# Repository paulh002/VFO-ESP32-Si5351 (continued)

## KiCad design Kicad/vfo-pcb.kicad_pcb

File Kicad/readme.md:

PCB files.
Added a pi attenuation circuit in the emmitor circuit of the driver transistors. The output level was sometimes to high creating spurs and AVC to react. Now it is possible to lower the output level by add in 6db attenuation. (This is optional if resistors are ommited you have full drive level).
To use this version with Wifi add a 4700 uf capacitor to the 5v line

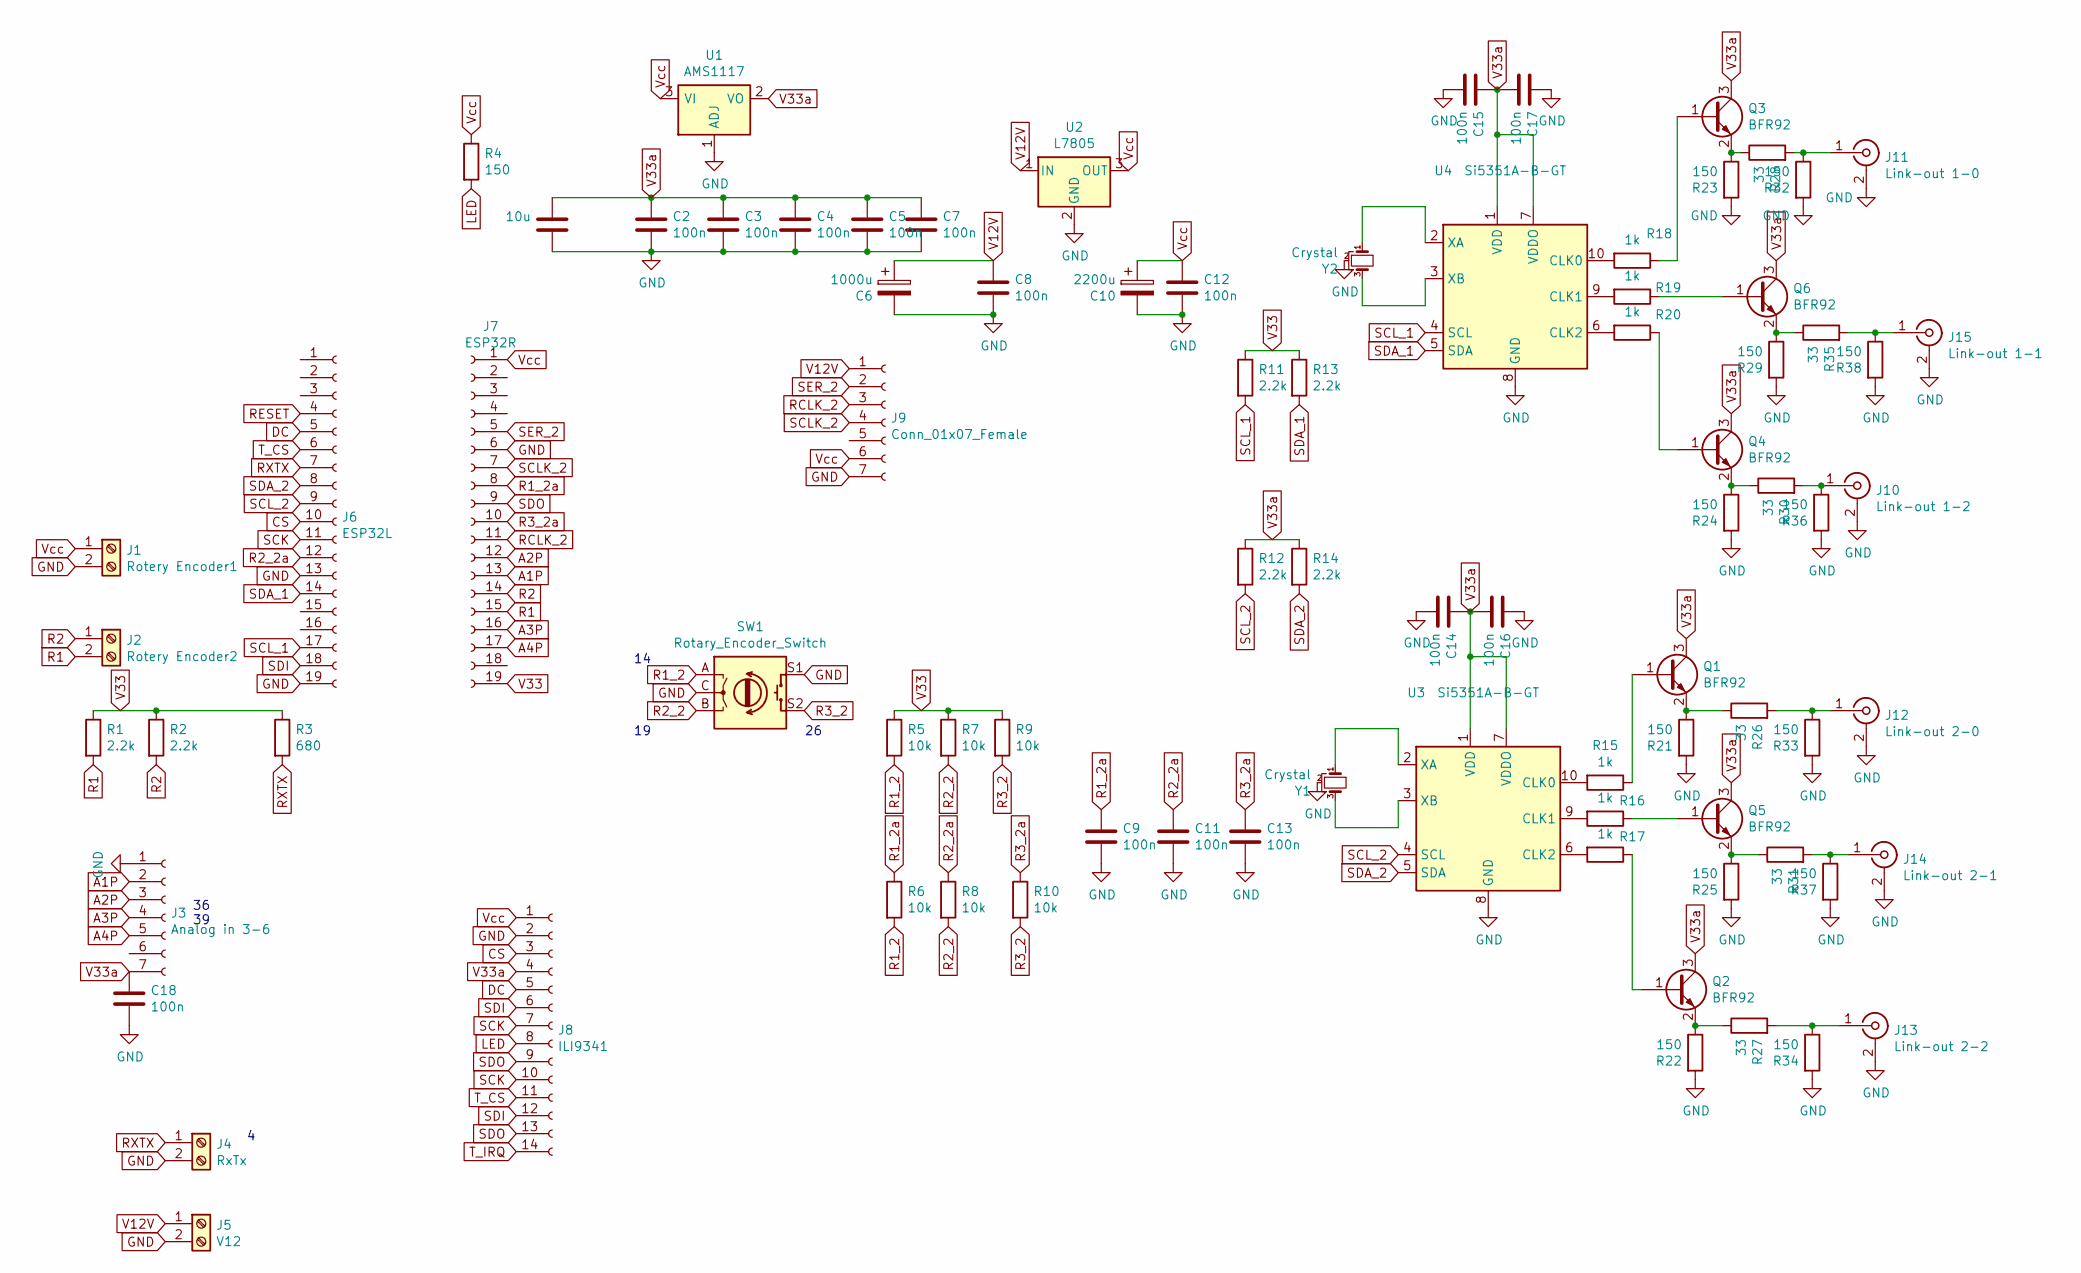
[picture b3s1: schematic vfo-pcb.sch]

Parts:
C1: 10u; C_1206_3216Metric_Pad1.42x1.75mm_HandSolder
C2, C3, C4, C5, C7, C8, C9, C11, C12, C13, C14, C15, C16, C17, C18: 100n; C_1206_3216Metric_Pad1.42x1.75mm_HandSolder
C6: 1000u; CP_Radial_D10.0mm_P5.00mm
C10: 2200u; CP_Radial_D10.0mm_P5.00mm
J1: Rotery Encoder1; TerminalBlock_MetzConnect_Type011_RT05502HBWC_1x02_P5.00mm_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
J2: Rotery Encoder2; TerminalBlock_MetzConnect_Type011_RT05502HBWC_1x02_P5.00mm_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
J3: Analog in 3-6; PinSocket_1x07_P2.54mm_Vertical
J4: RxTx; TerminalBlock_MetzConnect_Type011_RT05502HBWC_1x02_P5.00mm_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
J5: V12; TerminalBlock_MetzConnect_Type011_RT05502HBWC_1x02_P5.00mm_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
J6: ESP32L; PinSocket_1x19_P2.54mm_Vertical
J7: ESP32R; PinSocket_1x19_P2.54mm_Vertical
J8: ILI9341; PinSocket_1x14_P2.54mm_Vertical
J9: Conn_01x07_Female; PinSocket_1x07_P2.54mm_Vertical
J10: Link-out 1-2; SMA_Amphenol_132134_Vertical
J11: Link-out 1-0; SMA_Amphenol_132134_Vertical
J12: Link-out 2-0; SMA_Amphenol_132134_Vertical
J13: Link-out 2-2; SMA_Amphenol_132134_Vertical
J14: Link-out 2-1; SMA_Amphenol_132134_Vertical
J15: Link-out 1-1; SMA_Amphenol_132134_Vertical
Q1, Q2, Q3, Q4, Q5, Q6: BFR92; SOT-23
R1, R2, R11, R12, R13, R14: 2.2k; R_1206_3216Metric_Pad1.42x1.75mm_HandSolder
R3: 680; R_1206_3216Metric_Pad1.42x1.75mm_HandSolder
R4, R21, R22, R23, R24, R25, R29, R32, R33, R34, R36, R37, R38: 150; R_1206_3216Metric_Pad1.42x1.75mm_HandSolder
R5, R6, R7, R8, R9, R10: 10k; R_1206_3216Metric_Pad1.42x1.75mm_HandSolder
R15, R16, R17, R18, R19, R20: 1k; R_1206_3216Metric_Pad1.42x1.75mm_HandSolder
R26, R27, R28, R30, R31, R35: 33; R_1206_3216Metric_Pad1.42x1.75mm_HandSolder
SW1: Rotary_Encoder_Switch; RotaryEncoder_Alps_EC11E-Switch_Vertical_H20mm
U1: AMS1117; SOT-223-3_TabPin2
U2: L7805; TO-220-3_Vertical
U3, U4: Si5351A-B-GT; MSOP-10_3x3mm_P0.5mm
Y1, Y2: Crystal; Crystal_SMD_TXC_7M-4Pin_3.2x2.5mm_HandSoldering

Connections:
A1P: J3.2, J7.13
A2P: J3.3, J7.12
A3P: J3.4, J7.16
A4P: J3.5, J7.17
CS: J6.10, J8.3
DC: J6.5, J8.5
GND: C1.2, C2.1, C3.1, C4.1, C5.1, C6.2, C7.1, C8.1, C9.1, C10.2, C11.1, C12.1, C13.1, C14.1, C15.1, C16.2, C17.2, C18.1, J1.2, J3.1, J4.2, J5.2, J6.13, J6.19, J7.6, J8.2, J9.7, J10.2 (Ext), J11.2 (Ext), J12.2 (Ext), J13.2 (Ext), J14.2 (Ext), J15.2 (Ext), R21.2, R22.2, R23.2, R24.2, R25.2, R29.2, R32.2, R33.2, R34.2, R36.2, R37.2, R38.2, SW1.C, SW1.S1, U1.1 (ADJ), U2.2 (GND), U3.8 (GND), U4.8 (GND), Y1.2, Y2.2
LED: J8.8, R4.2
unnamed: J10.1 (In), R30.2, R36.1
unnamed: J11.1 (In), R28.2, R32.1
unnamed: J12.1 (In), R26.2, R33.1
unnamed: J13.1 (In), R27.2, R34.1
unnamed: J14.1 (In), R31.2, R37.1
unnamed: J15.1 (In), R35.2, R38.1
unnamed: Q1.1 (B), R15.1
unnamed: Q1.2 (E), R21.1, R26.1
unnamed: Q2.1 (B), R17.1
unnamed: Q2.2 (E), R22.1, R27.1
unnamed: Q3.1 (B), R18.1
unnamed: Q3.2 (E), R23.1, R28.1
unnamed: Q4.1 (B), R20.1
unnamed: Q4.2 (E), R24.1, R30.1
unnamed: Q5.1 (B), R16.1
unnamed: Q5.2 (E), R25.1, R31.1
unnamed: Q6.1 (B), R19.1
unnamed: Q6.2 (E), R29.1, R35.1
unnamed: R15.2, U3.10 (CLK0)
unnamed: R16.2, U3.9 (CLK1)
unnamed: R17.2, U3.6 (CLK2)
unnamed: R18.2, U4.10 (CLK0)
unnamed: R19.2, U4.9 (CLK1)
unnamed: R20.2, U4.6 (CLK2)
unnamed: U3.2 (XA), Y1.1
unnamed: U3.3 (XB), Y1.3
unnamed: U4.2 (XA), Y2.1
unnamed: U4.3 (XB), Y2.3
R1: J2.2, J7.15, R1.2
R1_2: R5.2, R6.2, SW1.A
R1_2a: C9.2, J7.8, R6.1
R2: J2.1, J7.14, R2.2
R2_2: R7.2, R8.2, SW1.B
R2_2a: C11.2, J6.12, R8.1
R3_2: R9.2, R10.2, SW1.S2
R3_2a: C13.2, J7.10, R10.1
RCLK_2: J7.11, J9.3
RESET: J6.4
RXTX: J4.1, J6.7, R3.2
SCK: J6.11, J8.7, J8.10
SCLK_2: J7.7, J9.4
SCL_1: J6.17, R11.2, U4.4 (SCL)
SCL_2: J6.9, R12.2, U3.4 (SCL)
SDA_1: J6.14, R13.2, U4.5 (SDA)
SDA_2: J6.8, R14.2, U3.5 (SDA)
SDI: J6.18, J8.6, J8.12
SDO: J7.9, J8.9, J8.13
SER_2: J7.5, J9.2
T_CS: J6.6, J8.11
T_IRQ: J8.14
V12V: C6.1, C8.2, J5.1, J9.1, U2.1 (IN)
V33: J7.19, R1.1, R2.1, R3.1, R5.1, R7.1, R9.1, R11.1, R13.1
V33a: C1.1, C2.2, C3.2, C4.2, C5.2, C7.2, C14.2, C15.2, C16.1, C17.1, C18.2, J3.7, J8.4, Q1.3 (C), Q2.3 (C), Q3.3 (C), Q4.3 (C), Q5.3 (C), Q6.3 (C), R12.1, R14.1, U1.2 (VO), U3.1 (VDD), U3.7 (VDDO), U4.1 (VDD), U4.7 (VDDO)
Vcc: C10.1, C12.2, J1.1, J7.1, J8.1, J9.6, R4.1, U1.3 (VI), U2.3 (OUT)

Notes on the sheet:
36 39

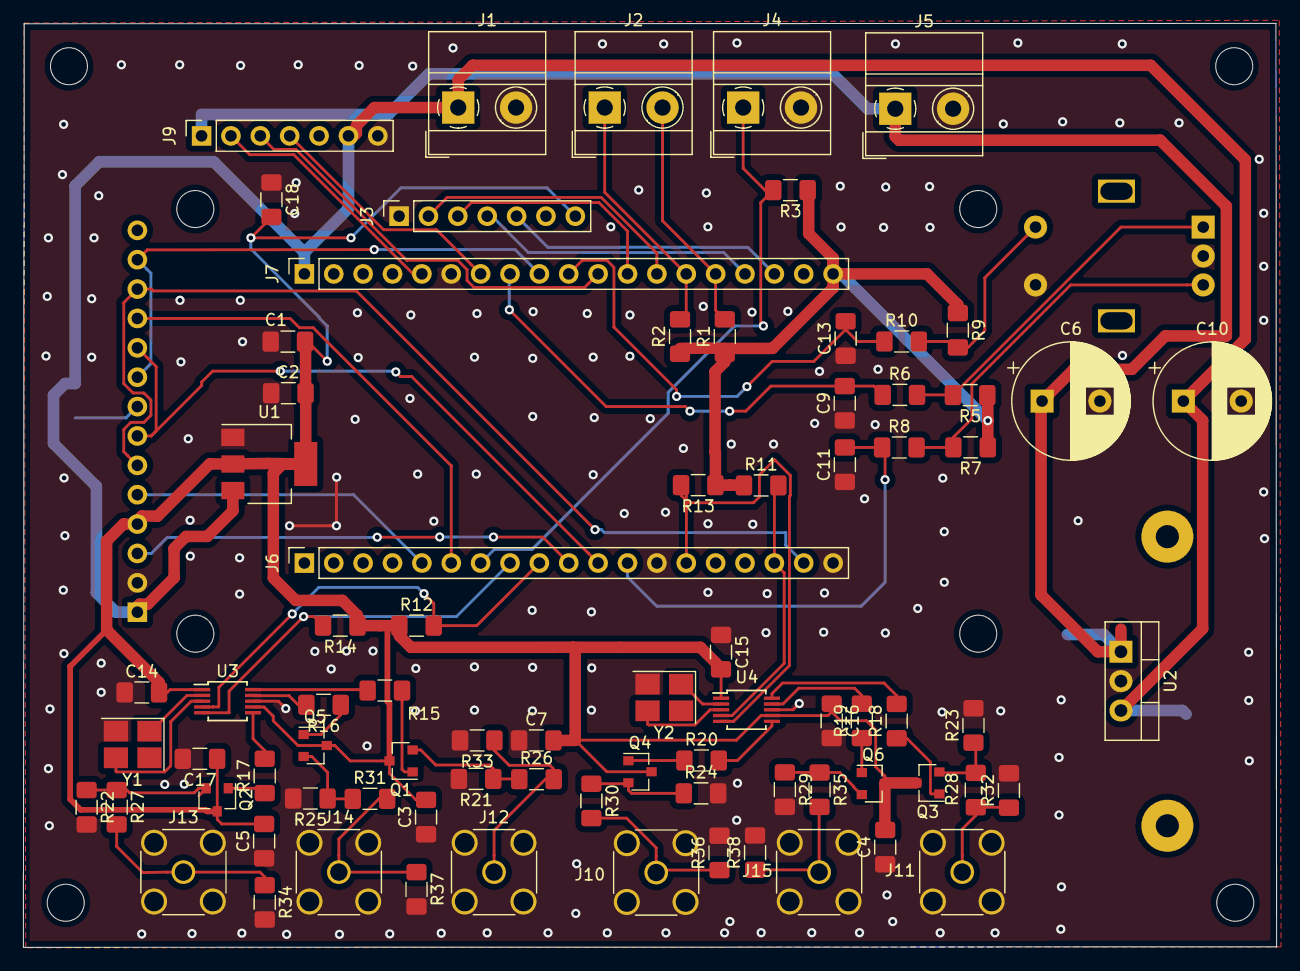
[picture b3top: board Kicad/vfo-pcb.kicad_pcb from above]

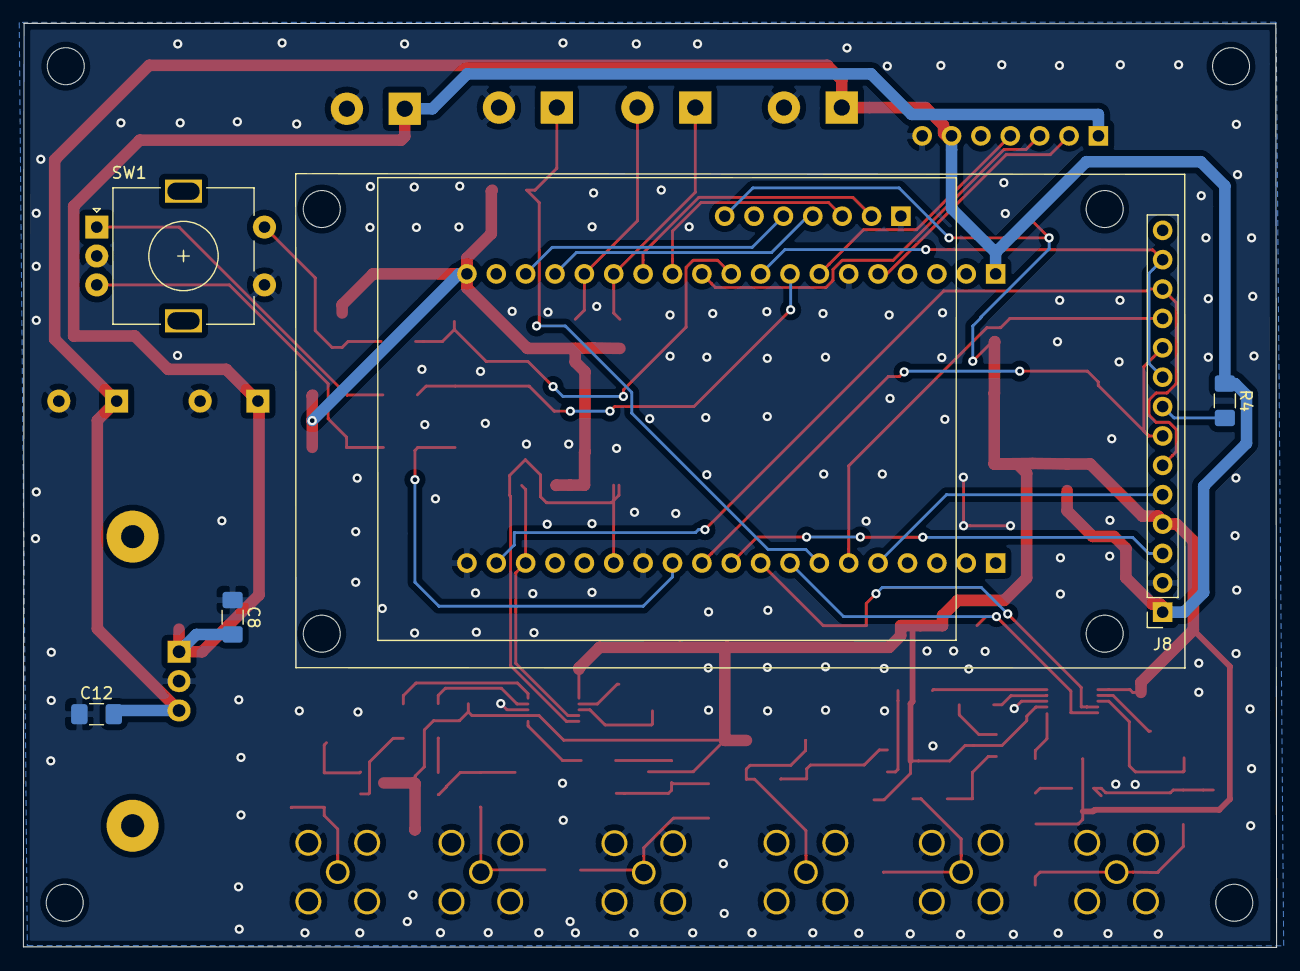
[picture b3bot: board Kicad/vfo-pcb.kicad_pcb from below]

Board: 2 copper layers, 108.4 x 79.9 mm, 94 parts (5 on the bottom side), 60 nets.

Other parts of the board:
 : MountingHole_3.2mm_M3
 #2,  #3: SolderWirePad_1x01_Drill2mm
 #4,  #5,  #6,  #7,  #8,  #9,  #10: MountingHole_3.2mm_M3

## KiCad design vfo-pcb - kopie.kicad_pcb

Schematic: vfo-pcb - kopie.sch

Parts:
C1, C3: 100u; CP_Radial_D8.0mm_P3.50mm
C2, C4, C8, C9, C10, C11, C12, C13: 100n; C_0805_2012Metric_Pad1.15x1.40mm_HandSolder
C5, C6, C7: 10n; C_0805_2012Metric_Pad1.15x1.40mm_HandSolder
J2: Conn_01x07_Female; PinSocket_1x07_P2.54mm_Vertical
J3: Si5351; PinSocket_1x07_P2.54mm_Vertical
J4: ESP32L; PinSocket_1x19_P2.54mm_Vertical
J5: ESP32R; PinSocket_1x19_P2.54mm_Vertical
J6: Rotery Encoder1; TerminalBlock_MetzConnect_Type011_RT05502HBWC_1x02_P5.00mm_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
J7: ILI9341; PinSocket_1x14_P2.54mm_Vertical
J8: Rotery Encoder2; TerminalBlock_MetzConnect_Type011_RT05502HBWC_1x02_P5.00mm_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
J9: Analog in 3-6; PinSocket_1x07_P2.54mm_Vertical
J10: Link-out 1a; SMA_Amphenol_132134_Vertical
J11: RxTx; TerminalBlock_MetzConnect_Type011_RT05502HBWC_1x02_P5.00mm_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
J13: Link-out 1b; SMA_Amphenol_132134_Vertical
J14: V12; TerminalBlock_MetzConnect_Type011_RT05502HBWC_1x02_P5.00mm_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
J17: Link-out 2a; SMA_Amphenol_132134_Vertical
J18: Link-out 3; SMA_Amphenol_132134_Vertical
J19: Link-out 2b; SMA_Amphenol_132134_Vertical
R1, R2, R7, R8, R9, R10: 2.2k; R_0805_2012Metric_Pad1.15x1.40mm_HandSolder
R3: 150; R_0805_2012Metric_Pad1.15x1.40mm_HandSolder
R4, R5, R6, R11, R12, R13: 10k; R_0805_2012Metric_Pad1.15x1.40mm_HandSolder
R14, R17, R20: 71; R_0805_2012Metric_Pad1.15x1.40mm_HandSolder
R15, R16, R18, R19, R21, R22: 100; R_0805_2012Metric_Pad1.15x1.40mm_HandSolder
SW1: Rotary_Encoder_Switch; RotaryEncoder_Alps_EC11E-Switch_Vertical_H20mm
U1, U4: AS179-92LF; SOT-363_SC-70-6
U2: 74HC595; DIP-16_W7.62mm_LongPads
U3: L7805; TO-220-3_Vertical

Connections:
A1P: J5.13, J9.2
A2P: J5.12, J9.3
A3P: J4.7, J9.4
A4P: J5.8, J9.5
A5P: J5.10, J9.6
A6P: J5.9, J9.7
CS: J4.10, J7.3
DC: J4.5, J7.5
Dout: J2.2, U2.9
GND: C1.2, C2.1, C3.2, C4.1, C5.1, C6.1, C7.1, J2.7, J3.2, J4.13, J4.19, J5.6, J6.2, J7.2, J9.1, J10.2 (Ext), J13.2 (Ext), J14.2, J17.2 (Ext), J18.2 (Ext), J19.2 (Ext), R15.2, R16.2, R18.2, R19.2, R21.2, R22.2, SW1.C, SW1.S1, U1.2, U2.8, U2.13, U3.2 (GND), U4.2
I1_1: J3.5, R20.2, R21.1
I2_1: J3.6, R17.2, R18.1
I3_1: J3.7, R14.2, R15.1
LED: J7.8, R3.2
unnamed: C8.1, R14.1, R16.1
unnamed: C8.2, U4.5
unnamed: C9.1, R17.1, R19.1
unnamed: C9.2, U1.5
unnamed: C10.1, U4.1
unnamed: C10.2, J13.1 (In)
unnamed: C11.1, U4.3
unnamed: C11.2, J10.1 (In)
unnamed: C12.1, U1.1
unnamed: C12.2, J19.1 (In)
unnamed: C13.1, U1.3
unnamed: C13.2, J17.1 (In)
unnamed: J18.1 (In), R20.1, R22.1
Qa: U1.4, U2.15, U4.4
Qb: U1.6, U2.1, U4.6
R1: J5.15, J8.2, R7.2
R1_2: R4.2, R11.2, SW1.A
R1_2a: C5.2, J4.9, R11.1
R2: J5.14, J8.1, R8.2
R2_2: R5.2, R12.2, SW1.B
R2_2a: C6.2, J4.12, R12.1
R3_2: R6.2, R13.2, SW1.S2
R3_2a: C7.2, J4.8, R13.1
RCLK_2: J2.3, J5.11, U2.12
RESET: J4.4, J7.4
RIT: J5.17, J11.2, R9.2
RXTX: J5.16, J11.1, R10.2
SCK: J4.11, J7.7
SCLK_2: J2.4, J5.7, U2.11
SCL_1: J3.4, J4.17, R1.2
SDA_1: J3.3, J4.14, R2.2
SDI: J4.18, J7.6
SDO: J7.9
SER_2: J5.5, U2.14
T_CLK: J7.10
T_CS: J7.11
T_D0: J7.13
T_DIN: J7.12
T_IRQ: J7.14
V12V: C1.1, C2.2, J2.1, J14.1, U3.1 (IN)
V33: J3.1, J5.19, R1.1, R2.1, R4.1, R5.1, R6.1, R7.1, R8.1, R9.1, R10.1
Vcc: C3.1, C4.2, J2.6, J5.1, J6.1, J7.1, R3.1, U2.10, U2.16, U3.3 (OUT)

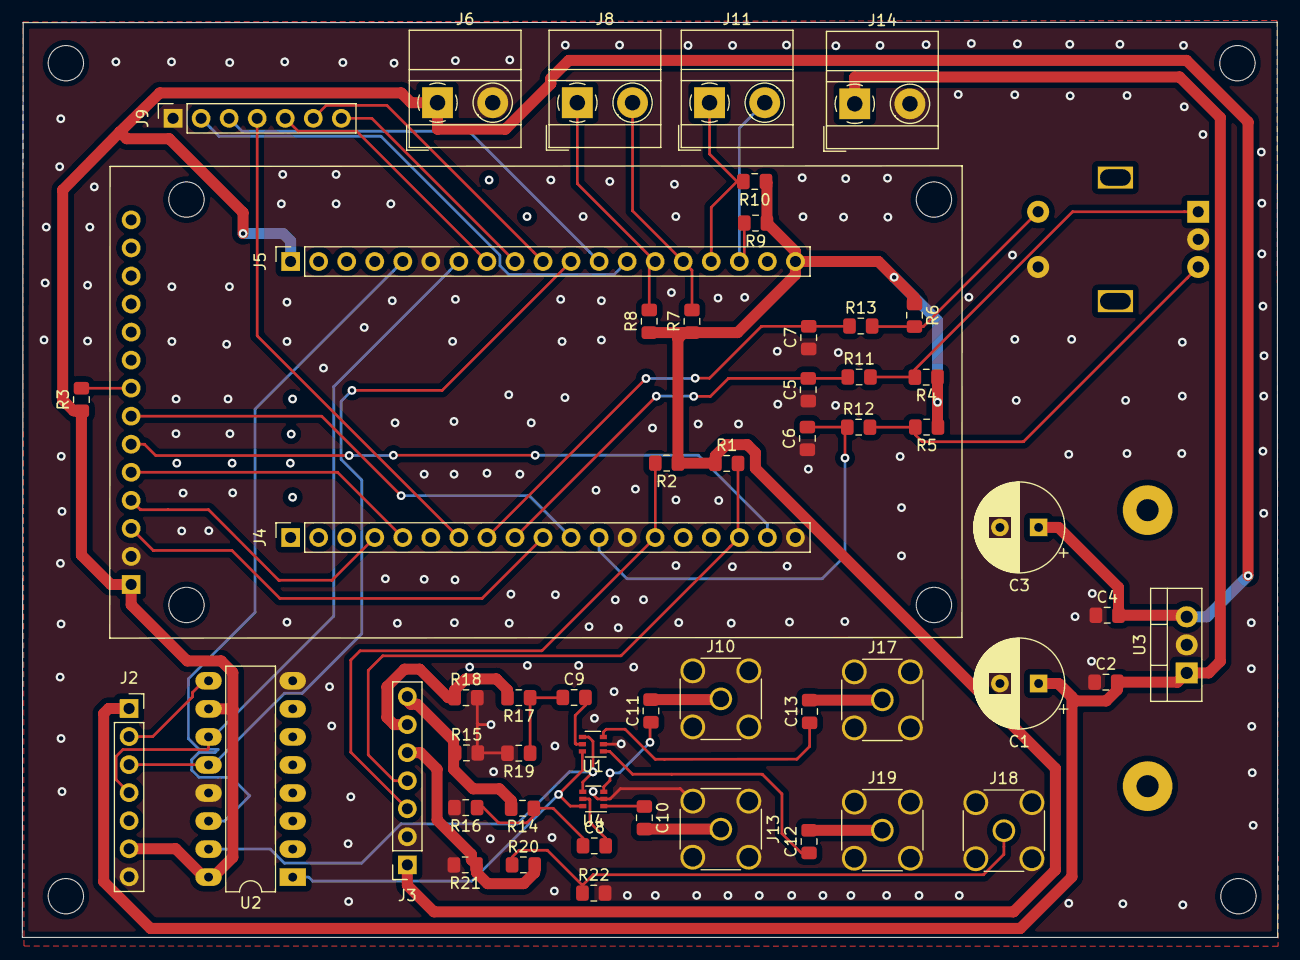
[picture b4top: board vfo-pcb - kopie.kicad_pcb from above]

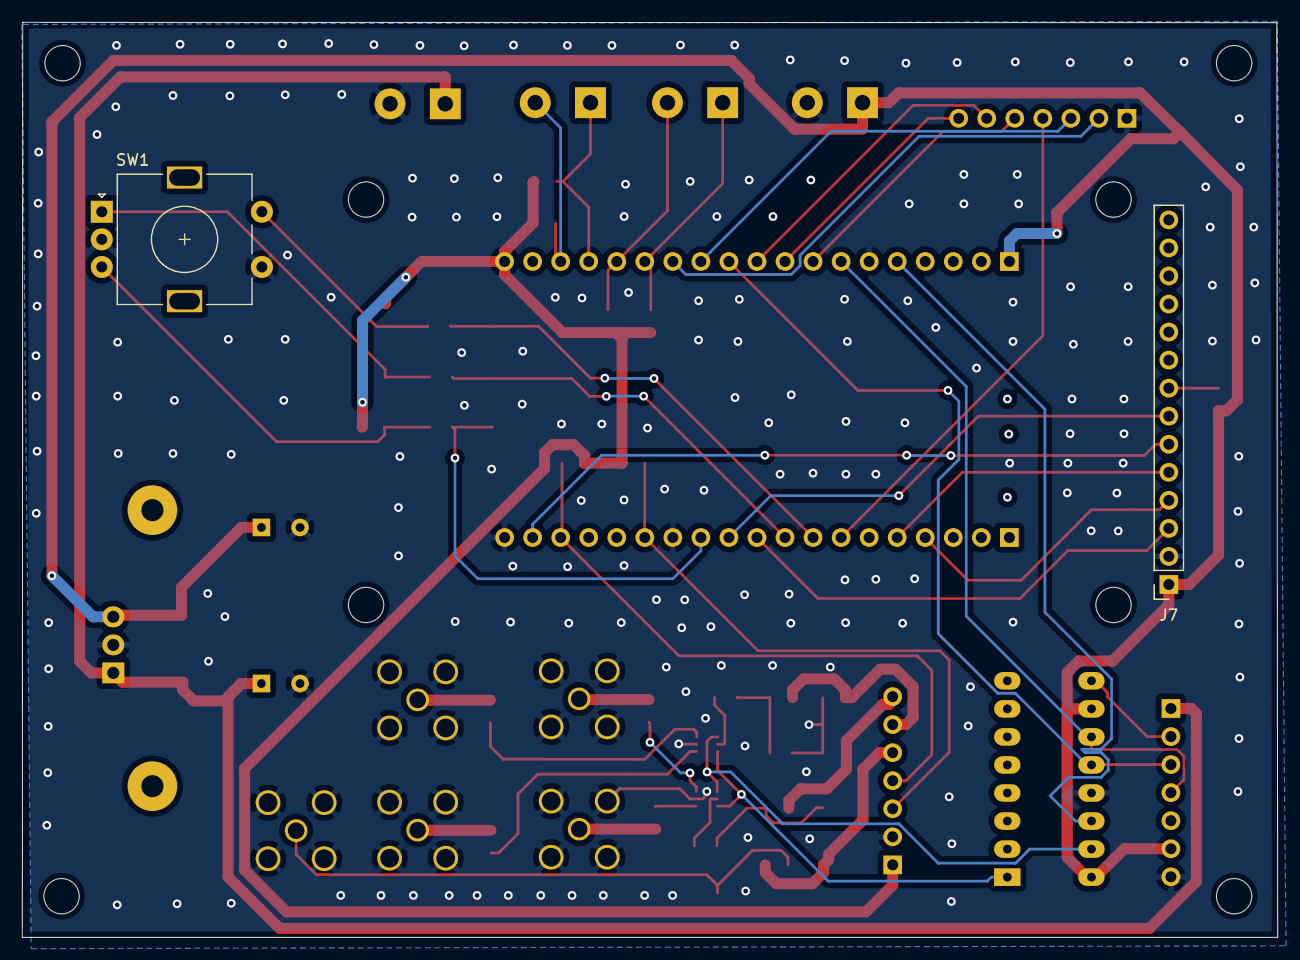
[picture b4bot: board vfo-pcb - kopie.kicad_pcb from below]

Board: 2 copper layers, 113.7 x 82.9 mm, 65 parts (2 on the bottom side), 50 nets.

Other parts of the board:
 : MountingHole_3.2mm_M3
 #2,  #3: SolderWirePad_1x01_Drill2mm
 #4,  #5,  #6,  #7,  #8,  #9,  #10: MountingHole_3.2mm_M3

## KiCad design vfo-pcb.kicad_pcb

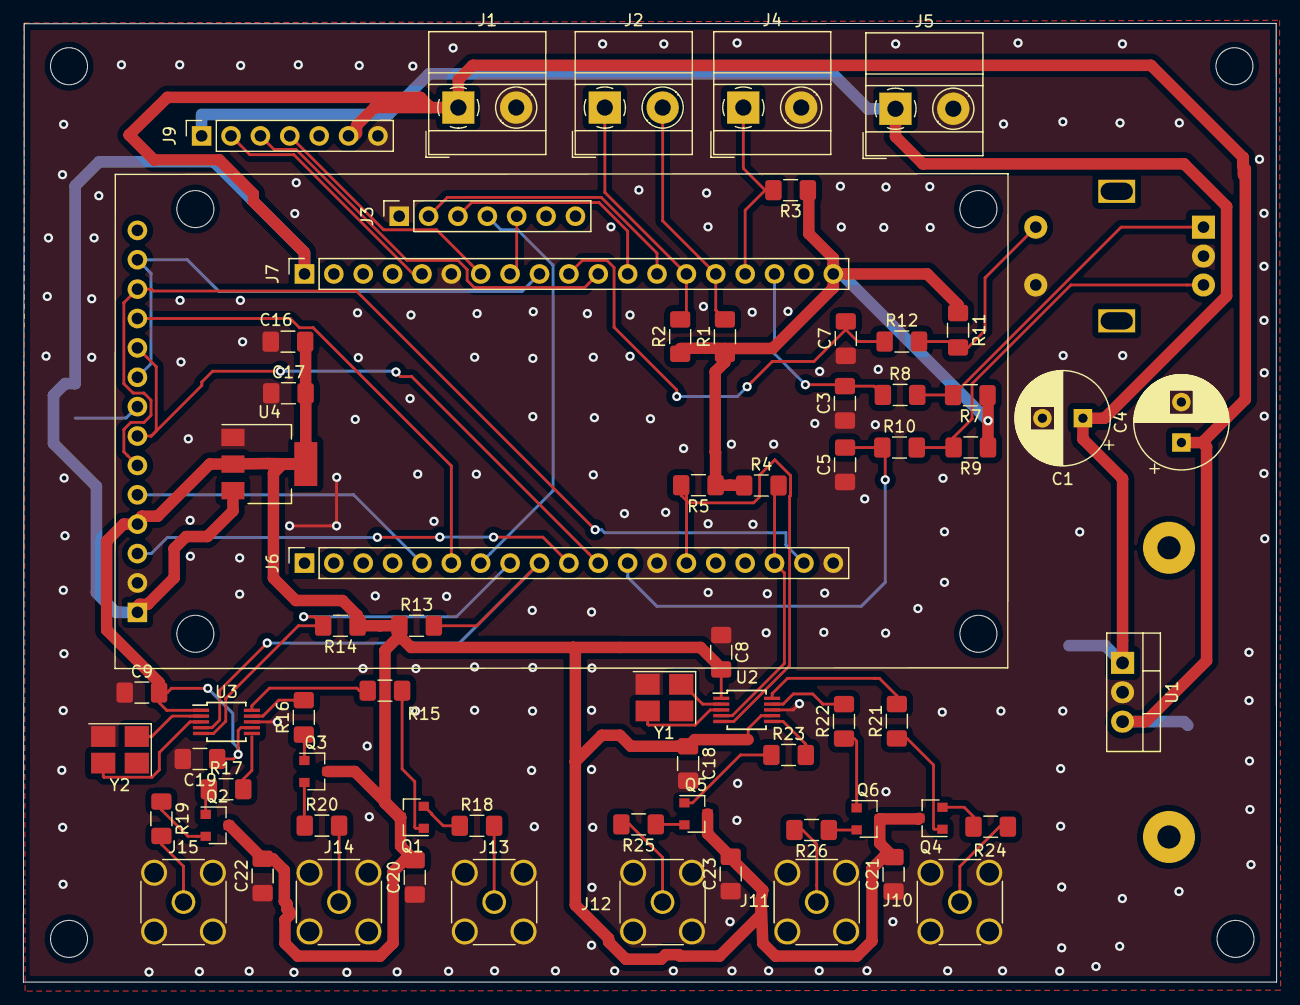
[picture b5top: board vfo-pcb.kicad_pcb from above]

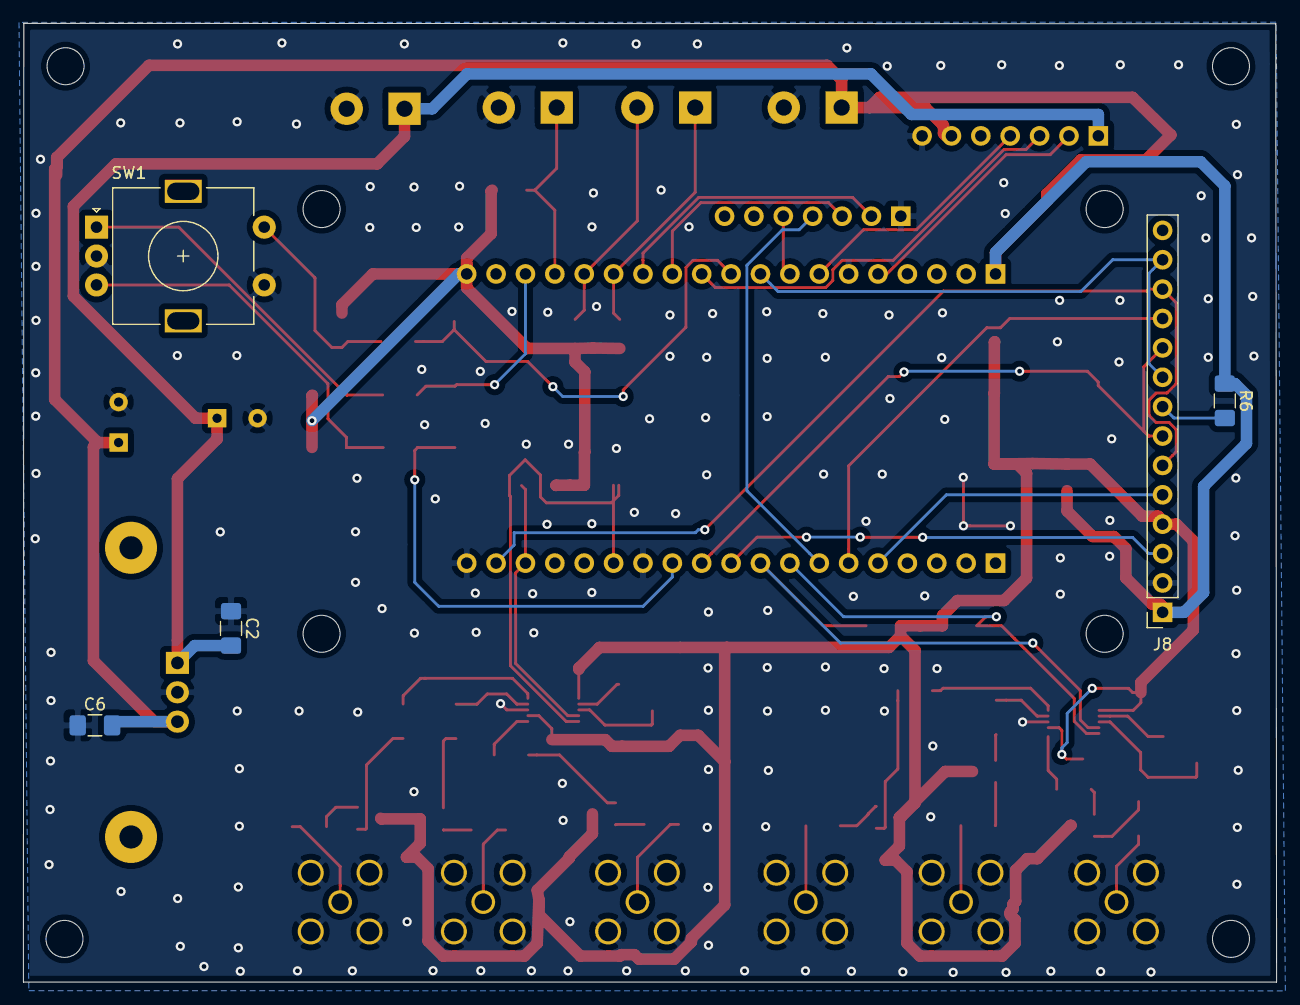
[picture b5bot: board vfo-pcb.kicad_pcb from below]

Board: 2 copper layers, 108.3 x 82.9 mm, 81 parts (5 on the bottom side), 60 nets.

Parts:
 : MountingHole_3.2mm_M3
 #2,  #3: SolderWirePad_1x01_Drill2mm
 #4,  #5,  #6,  #7,  #8,  #9,  #10: MountingHole_3.2mm_M3
C1, C4: 100u; CP_Radial_D8.0mm_P3.50mm
C2, C6, C8, C9, C17, C18, C19, C20, C21, C22, C23: 100n; C_1206_3216Metric_Pad1.42x1.75mm_HandSolder
C3, C5, C7: 10n; C_1206_3216Metric_Pad1.42x1.75mm_HandSolder
C16: 10u; C_1206_3216Metric_Pad1.42x1.75mm_HandSolder
J1: Rotery Encoder1; TerminalBlock_MetzConnect_Type011_RT05502HBWC_1x02_P5.00mm_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
J2: Rotery Encoder2; TerminalBlock_MetzConnect_Type011_RT05502HBWC_1x02_P5.00mm_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
J3: Analog in 3-6; PinSocket_1x07_P2.54mm_Vertical
J4: RxTx; TerminalBlock_MetzConnect_Type011_RT05502HBWC_1x02_P5.00mm_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
J5: V12; TerminalBlock_MetzConnect_Type011_RT05502HBWC_1x02_P5.00mm_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
J6: ESP32L; PinSocket_1x19_P2.54mm_Vertical
J7: ESP32R; PinSocket_1x19_P2.54mm_Vertical
J8: ILI9341; PinSocket_1x14_P2.54mm_Vertical
J9: Conn_01x07_Female; PinSocket_1x07_P2.54mm_Vertical
J10: Link-out 1-0; SMA_Amphenol_132134_Vertical
J11: Link-out 1-1; SMA_Amphenol_132134_Vertical
J12: Link-out 1-2; SMA_Amphenol_132134_Vertical
J13: Link-out 2-0; SMA_Amphenol_132134_Vertical
J14: Link-out 2-1; SMA_Amphenol_132134_Vertical
J15: Link-out 2-2; SMA_Amphenol_132134_Vertical
Q1, Q2, Q3, Q4, Q5, Q6: BFR92; SOT-23
R1, R2, R3, R4, R5, R13, R14: 2.2k; R_1206_3216Metric_Pad1.42x1.75mm_HandSolder
R6: 150; R_1206_3216Metric_Pad1.42x1.75mm_HandSolder
R7, R8, R9, R10, R11, R12: 10k; R_1206_3216Metric_Pad1.42x1.75mm_HandSolder
R15, R16, R17, R21, R22, R23: 1k; R_1206_3216Metric_Pad1.42x1.75mm_HandSolder
R18, R19, R20, R24, R25: 20; R_1206_3216Metric_Pad1.42x1.75mm_HandSolder
R26: 47; R_1206_3216Metric_Pad1.42x1.75mm_HandSolder
SW1: Rotary_Encoder_Switch; RotaryEncoder_Alps_EC11E-Switch_Vertical_H20mm
U1: L7805; TO-220-3_Vertical
U2, U3: Si5351A-B-GT; MSOP-10_3x3mm_P0.5mm
U4: AMS1117; SOT-223-3_TabPin2
Y1, Y2: Crystal; Crystal_SMD_TXC_7M-4Pin_3.2x2.5mm_HandSoldering

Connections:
A1P: J3.2, J7.13
A2P: J3.3, J7.12
A3P: J3.4, J6.7
A4P: J3.5, J7.8
CS: J6.10, J8.3
DC: J6.5, J8.5
GND: C1.2, C2.1, C3.1, C4.2, C5.1, C6.1, C7.1, C8.1, C9.1, C16.2, C17.1, C18.2, C19.2, C20.1, C21.1, C22.1, C23.1, J1.2, J3.1, J4.2, J5.2, J6.13, J6.19, J7.6, J8.2, J9.7, J10.2, J11.2, J12.2, J13.2, J14.2, J15.2, SW1.C, SW1.S1, U1.2, U2.8, U3.8, U4.1, Y1.2, Y2.2
LED: J8.8, R6.2
unnamed: J10.1, R24.2
unnamed: J11.1, R26.2
unnamed: J12.1, R25.2
unnamed: J13.1, R18.2
unnamed: J14.1, R20.2
unnamed: J15.1, R19.2
unnamed: Q1.1, R15.1
unnamed: Q1.2, R18.1
unnamed: Q2.1, R17.1
unnamed: Q2.2, R19.1
unnamed: Q3.1, R16.1
unnamed: Q3.2, R20.1
unnamed: Q4.1, R21.1
unnamed: Q4.2, R24.1
unnamed: Q5.1, R23.1
unnamed: Q5.2, R25.1
unnamed: Q6.1, R22.1
unnamed: Q6.2, R26.1
unnamed: R15.2, U3.10
unnamed: R16.2, U3.9
unnamed: R17.2, U3.6
unnamed: R21.2, U2.10
unnamed: R22.2, U2.9
unnamed: R23.2, U2.6
unnamed: U2.2, Y1.1
unnamed: U2.3, Y1.3
unnamed: U3.2, Y2.1
unnamed: U3.3, Y2.3
R1: J2.2, J7.15, R1.2
R1_2: R7.2, R8.2, SW1.A
R1_2a: C3.2, J7.17, R8.1
R2: J2.1, J7.14, R2.2
R2_2: R9.2, R10.2, SW1.B
R2_2a: C5.2, J6.12, R10.1
R3_2: R11.2, R12.2, SW1.S2
R3_2a: C7.2, J7.10, R12.1
RCLK_2: J7.11, J9.3
RXTX: J4.1, J7.16, R3.2
SCK: J6.11, J8.7, J8.10
SCLK_2: J7.7, J9.4
SCL_1: J6.17, R4.2, U2.4
SCL_2: J6.9, R13.2, U3.4
SDA_1: J6.14, R5.2, U2.5
SDA_2: J6.8, R14.2, U3.5
SDI: J6.18, J8.6, J8.12
SDO: J7.9, J8.9, J8.13
SER_2: J7.5, J9.2
T_CS: J6.6, J8.11
V12V: C1.1, C2.2, J5.1, J9.1, U1.1
V33: J7.19, R1.1, R2.1, R3.1, R4.1, R5.1, R7.1, R9.1, R11.1
V33a: C8.2, C9.2, C16.1, C17.2, C18.1, C19.1, C20.2, C21.2, C22.2, C23.2, J8.4, Q1.3, Q2.3, Q3.3, Q4.3, Q5.3, Q6.3, R13.1, R14.1, U2.1, U2.7, U3.1, U3.7, U4.2
Vcc: C4.1, C6.2, J1.1, J7.1, J8.1, J9.6, R6.1, U1.3, U4.3

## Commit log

2020-05-10 Fixed click noise issues
    Removed pll reset and moved output 1 and 2 to PLL B
2020-05-10 added some crosstalk comments
2020-05-10 Crosstalk measurement
    The crosstalk measured is about -52db Clock 0 12Mhz, Clock 1 8.998 Mhz
2020-05-10 crosstalk improvement
2020-05-10 Attenuator removed
    To improve crosstalk the attenuators are removed and replaced by 100nF DC blocker
2020-05-10 attenuators removed
2020-06-13 Add files via upload
    2 si5351 spectrum
2020-09-03 Fixed RX TX switching and remember vfo frequency when band is switched
2020-09-04 Add files via upload
    Updated output circuit added pi attenuation
2020-09-06 Added multi switch to adjust bfo
2020-09-14 Updated bfo switching
    When the software start, the tx bfo stayed swiched on until a rx/tx switch happend. This due to auto output enable of SI5351 library.
2020-10-28 SWR extension and Calibration
2020-10-28 Pre version for SWR support
    ! not yet final
2020-10-28 Fonts not part of adafruit library
2020-12-07 added CAT serial interface
2020-12-07 Added CAT interface
2021-01-04 Added wifi update support
2021-01-04 Wifi update support
2021-01-17 Create kicad2
2021-01-17 Wifi and buck converter version pcb
2021-01-17 wifi update LM7805 version
2021-01-17 wifi support and GPIO changes
2021-01-17 wifi update
2021-02-21 update wifi pcb
2021-03-05 New PCB for JTAG
2021-03-05 jtag interface
2021-03-06 Network CAT
2021-03-06 Network CAT and updated ota
2021-03-07 Network performance fix
2021-03-09 Update wifi network functions
2021-03-09 Network update
2021-03-09 minor fixes
2021-03-16 lvgl userinterface
2021-03-16 software changes
2021-03-22 lvgl update
2021-03-22 lvgl update 2
2021-03-22 CAT update
2021-03-24 added swr and pwr gauges
2021-04-03 update calibration gui
2021-04-03 change debounce
2021-04-07 GUI update
2021-04-13 setup GUI update
2021-04-14 add credentials.h
2021-04-16 bfo gui update
2021-05-04 4 layer PCB
2021-05-04 TCA9584
2021-05-28 v3 version
2021-05-31 band select fixes
2021-10-14 new pcb
2021-10-18 readme
2021-11-13 update pcb
2023-06-28 close repo
